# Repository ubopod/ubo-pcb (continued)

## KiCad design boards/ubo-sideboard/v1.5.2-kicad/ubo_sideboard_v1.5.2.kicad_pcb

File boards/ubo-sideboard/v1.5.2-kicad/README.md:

# Side Connector Board
This depo contain KiCad design files for PCB that connects to Raspberry Pi 4 and 5 side connectors, 
namely mini HDMIs, USB-C power, and audio jack (on Pi 4). The Pi 5 variant does not have the audio plug 
populated on the PCB since Pi 5 does not have an audio jack.

<table>
  <tr>
    <td></td>
    <td></td>
  </tr>
</table>

This design is used in [Ubo Pod](https://getubo.com) with a custom enclosure to arrange all the ports on the back:

## Features
- Mini HDMI to full HDMI conversion
- MicroSD card reader extender (brings the reader to the back)
- Audio jack insertion detection (via GPIO)
- Internal USB Type A connector that connects to data lines on USB-C
- 2 STEMMA Qt connectors (one internal and one external)
- Power button 
- Fan connector
- 2x8 Pin Header that connects to:
   - I2C pins
   - 3.3v and 5v pins
   - Right and left speakers
   - Audio line in (connects to audio jack)
   - Fan control
   - Power button
   - Audio insersion jack
   - 1 unused GPIO
 
## Layout

## Schematic

TODO:
- Add BOM
- Add stackup and manufacturing information

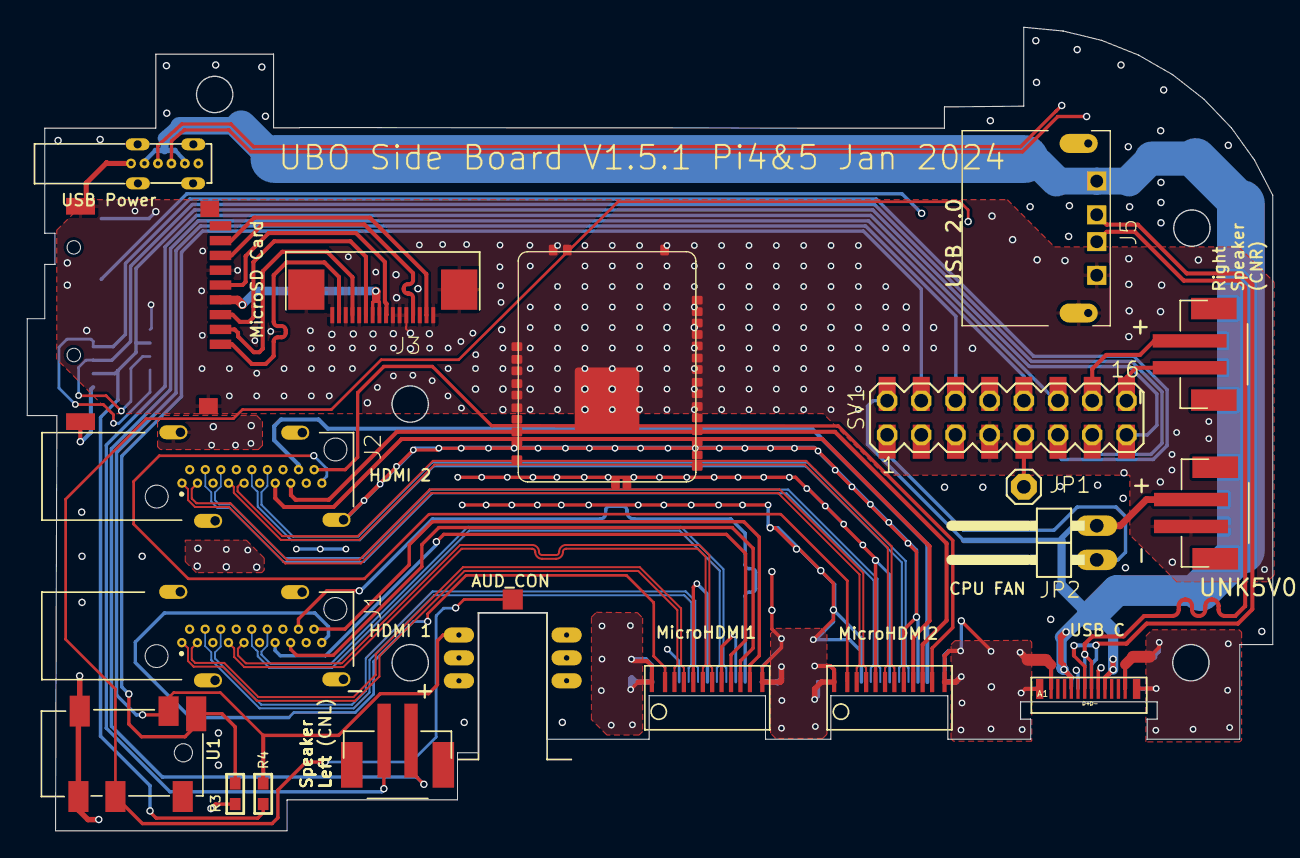
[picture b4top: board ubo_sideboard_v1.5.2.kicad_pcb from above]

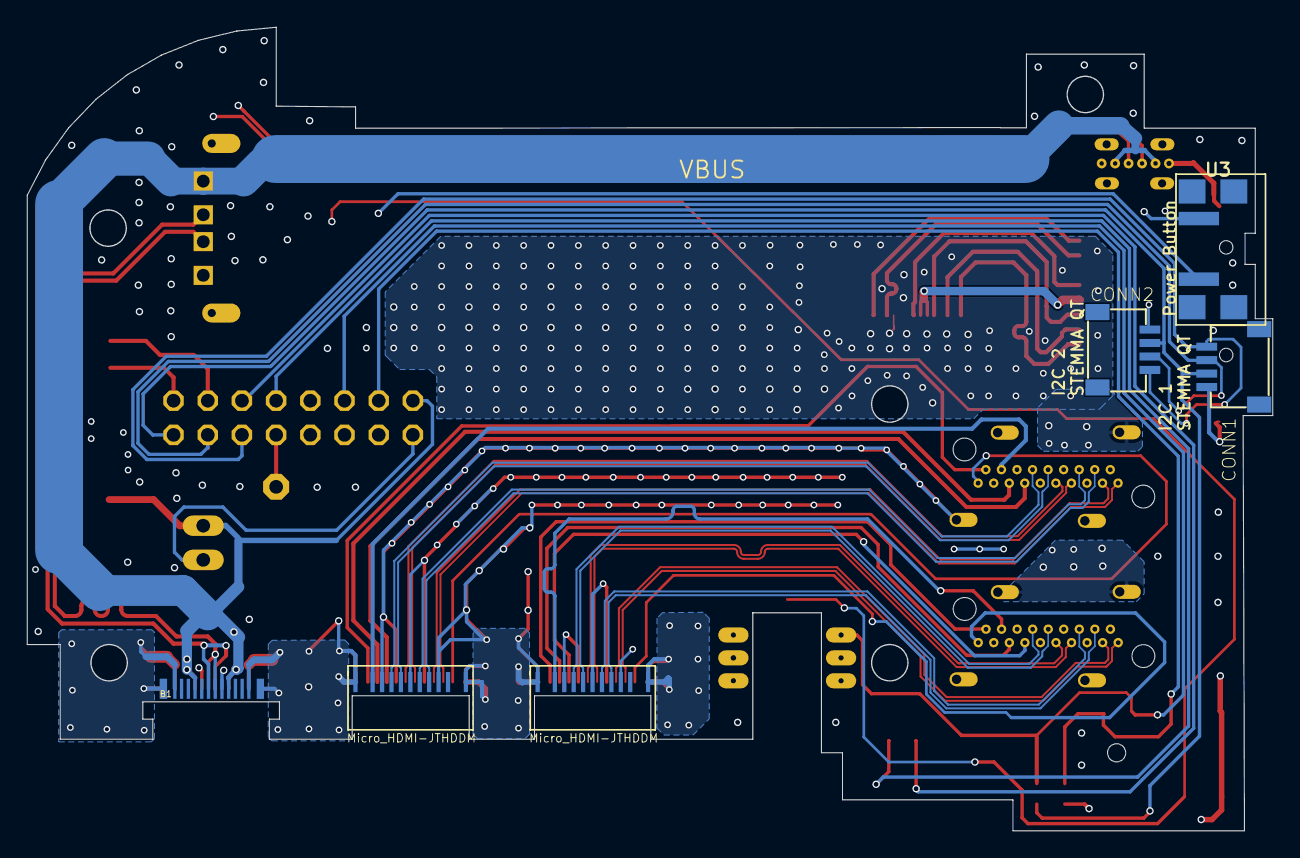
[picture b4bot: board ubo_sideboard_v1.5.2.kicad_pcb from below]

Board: 4 copper layers, 92.5 x 59.7 mm, 23 parts (5 on the bottom side), 53 nets.

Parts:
AUD_CON0: AUDIO_3.5MMJACK_MALE; AUDIO_3.5MM_JACK_MALE_28380031
CN_SPK_L0: JST-PH-2-SMT_28380031
CN_SPK_R0: JST-PH-2-SMT_28380031
CONN1, CONN2: STEMMA_I2C_QT; JST_SH4_28380031
J1, J2: HDMI-KDMIX-SL1-NS-WS-B15; CONN_KDMIX-SL1-NS-WS-B15_28380031
J3: FPC_16PIN; FPC_16PIN_05MM_28380031
J5: USB-A-S-X-X-SM2RA03B-DT98; USB-A-RA03B-DT98_28380031
JP1: 1X01_420
JP2: 1X02_90_325
MICROHDMI1, MICROHDMI2: MICRO_HDMI_JTHDDM; MICRO_HDMI_JTHDDM_28380031
R3: 100K; _0603_28380031
R4: 1K; _0603_28380031
SV1: MA08X2-FEMALE_28380031
U1: AUDIO_SOCKET_JHP_328BPJ-3160; PJ-3160_28380031
U2: USB-20C-F-06CD-1; USB_20C_F_60CD_28380031
U3: TS06105SA; TS-06105SA-1_28380031
U4: MICROSDTF01-H1.8; MICROSDTF-01-H1.8_28380031
U*: melonHD_SMT
UNK5V0: 5V; JST-PH-2-SMT_28380031
USBC0: USB_TYPE_MALE_31C_J10C; USB_TYPE_MALE_31C_J10A_28380031

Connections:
3.3V: CONN1.2, CONN2.2, R4.2, SV1.15, SV1.P$15
5V_A: J1.18, MICROHDMI1.19
5V_B: J2.18, MICROHDMI2.19
A5: U2.A5, USBC0.A5
B5: U2.B5, USBC0.B5
CEC_A: J1.13, MICROHDMI1.15
CEC_B: J2.13, MICROHDMI2.15
CLK_SD: J3.8, U4.P$5
CMD_SD: J3.11, U4.P$3
DAT0: J3.4, U4.P$7
DAT1: J3.2, U4.P$8
DAT2: J3.15, U4.P$1
DAT3: J3.13, U4.P$2
DDC_CLOCK_A: J1.15, MICROHDMI1.17
DDC_CLOCK_B: J2.15, MICROHDMI2.17
DDC_DATA_A: J1.16, MICROHDMI1.18
DDC_DATA_B: J2.16, MICROHDMI2.18
D_N: J5.P$2, USBC0.A7, USBC0.B7
D_P: J5.P$3, USBC0.A6, USBC0.B6
FAN_OUT: JP2.1, SV1.1, SV1.P$1
GND: AUD_CON0.P$1L, AUD_CON0.P$1R, AUD_CON0.P$2L, AUD_CON0.P$2R, CONN1.1, CONN2.1, J1.2, J1.5, J1.8, J1.11, J1.17, J1.S1, J1.S2, J1.S3, J1.S4, J2.2, J2.5, J2.8, J2.11, J2.17, J2.S1, J2.S2, J2.S3, J2.S4, J3.1, J3.3, J3.5, J3.6, J3.7, J3.12, J3.14, J3.16, J3.Z1, J3.Z2, J5.P$4, J5.SH$1, J5.SH$2, MICROHDMI1.4, MICROHDMI1.7, MICROHDMI1.10, MICROHDMI1.13, MICROHDMI1.16, MICROHDMI1.S1, MICROHDMI1.S2, MICROHDMI1.S3, MICROHDMI1.S4, MICROHDMI2.4, MICROHDMI2.7, MICROHDMI2.10, MICROHDMI2.13, MICROHDMI2.16, MICROHDMI2.S1, MICROHDMI2.S2, MICROHDMI2.S3, MICROHDMI2.S4, R3.1, SV1.7, SV1.P$7, U1.1, U1.2, U2.A12, U2.B12, U2.P$1, U2.P$2, U2.P$3, U2.P$4, U3.A, U4.GND$1, U4.GND$2, U4.GND$3, U4.GND$4, U4.P$6, UNK5V0.2, USBC0.A1, USBC0.A12, USBC0.B1, USBC0.B12, USBC0.SH$1, USBC0.SH$2, USBC0.SH$3, USBC0.SH$4
GPIO17: SV1.5, SV1.P$5
GPIO27: SV1.3, SV1.P$3, U3.B
HOT_PLUG_A: J1.19, MICROHDMI1.1
HOT_PLUG_B: J2.19, MICROHDMI2.1
HP_DETECT: R3.2, SV1.4, SV1.P$4, U1.6
LINEOUT_L: AUD_CON0.P$3L, AUD_CON0.P$3R, R4.1, SV1.6, SV1.P$6, U1.4
LINEOUT_R: AUD_CON0.P$4, SV1.8, SV1.P$8, U1.3
unnamed: JP1.1, SV1.9, SV1.P$9
SCL: CONN1.4, CONN2.4, SV1.11, SV1.P$11
SDA: CONN1.3, CONN2.3, SV1.13, SV1.P$13
SPK_LN: CN_SPK_L0.2, SV1.12, SV1.P$12
SPK_LP: CN_SPK_L0.1, SV1.10, SV1.P$10
SPK_RN: CN_SPK_R0.2, SV1.16, SV1.P$16
SPK_RP: CN_SPK_R0.1, SV1.14, SV1.P$14
TMDS_CLOCK_A_N: J1.12, MICROHDMI1.14
TMDS_CLOCK_A_P: J1.10, MICROHDMI1.12
TMDS_CLOCK_B_N: J2.12, MICROHDMI2.14
TMDS_CLOCK_B_P: J2.10, MICROHDMI2.12
TMDS_D0_A_N: J1.9, MICROHDMI1.11
TMDS_D0_A_P: J1.7, MICROHDMI1.9
TMDS_D0_B_N: J2.9, MICROHDMI2.11
TMDS_D0_B_P: J2.7, MICROHDMI2.9
TMDS_D1_A_N: J1.6, MICROHDMI1.8
TMDS_D1_A_P: J1.4, MICROHDMI1.6
TMDS_D1_B_N: J2.6, MICROHDMI2.8
TMDS_D1_B_P: J2.4, MICROHDMI2.6
TMDS_D2_A_N: J1.3, MICROHDMI1.5
TMDS_D2_A_P: J1.1, MICROHDMI1.3
TMDS_D2_B_N: J2.3, MICROHDMI2.5
TMDS_D2_B_P: J2.1, MICROHDMI2.3
VBUS: J5.P$1, JP2.2, SV1.2, SV1.P$2, U2.A9, U2.B9, UNK5V0.1, USBC0.A4, USBC0.A9, USBC0.B4, USBC0.B9
VDD_SD: J3.9, J3.10, U4.P$4

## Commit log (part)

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2023-02-27 added PCB schematic
    will add layout and other files soon
2023-03-11 added datasheets and images
2023-03-11 added more images
2023-04-07 Top PCB DFX Dimensions
2023-04-07 Top PCB Step file 3D model
2023-04-07 added top PCB schematic and layout design files
2023-04-07 added top pcb design files
2023-04-08 changed filename
2023-04-08 moved schematic files to schematic
2023-04-08 moved files
2025-07-29 adding KiCad design files for sideboard v1.5.2
2025-07-29 added schematic image
2025-07-29 updated 3d image
2025-08-29 added M.2 M-key to A/E-key adapter
2025-08-29 added real images for m-key adapter
2025-08-29 add ubo images with adapter and coral
2025-08-29 Enhance README with images and usage information
    Added images and details about the M.2 M-key to A/E-key adapter and its application in Ubo Pod.
2025-08-29 add design files for PCIe adapter
2025-08-29 add readme
2025-08-29 Update README with PCIe adapter details and images
    Added detailed description and images for the PCIe adapter board.
2025-09-03 Enhance README with Ubo Pod details and images
2025-09-03 Fix image paths in Ubo Pod README
2025-09-03 Update README with design inspiration attribution
2025-09-03 add S-shaped FPC cable design
2025-09-03 Enhance README with link and images for FPC cable
    Added link to the PCIe adapter board repository and included images of the FPC cable.
2026-01-17 add new PCIe HAB v2 design
2026-01-18 Add README for Ubo HAB adapter board
    Added detailed README for Ubo HAB PCIe/USB-C/POE+ adapter board, including features, purchasing information, and power module details.
2026-01-18 add images for ubo hab and modules
2026-01-18 Revise power module links in README
    Updated links for power modules in the README.
2026-04-22 add ubo nfc hat design files
2026-04-22 removed unused directory
